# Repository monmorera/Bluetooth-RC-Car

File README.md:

# Bluetooth-RC-Car
### Bluetooth RC Car project for ECE 196 course

#### About:
This project is to create a bluetooth radio-controlled car. The PCB for the vehicle and remote was created and designed with EAGLE. It was then programmed using Arduino. The remote casing and vehicle parts were created and assembled in SolidWorks. Some parts were 3D printed and others laser cut.

##### Vehicle:

##### Remote:

##### Final:

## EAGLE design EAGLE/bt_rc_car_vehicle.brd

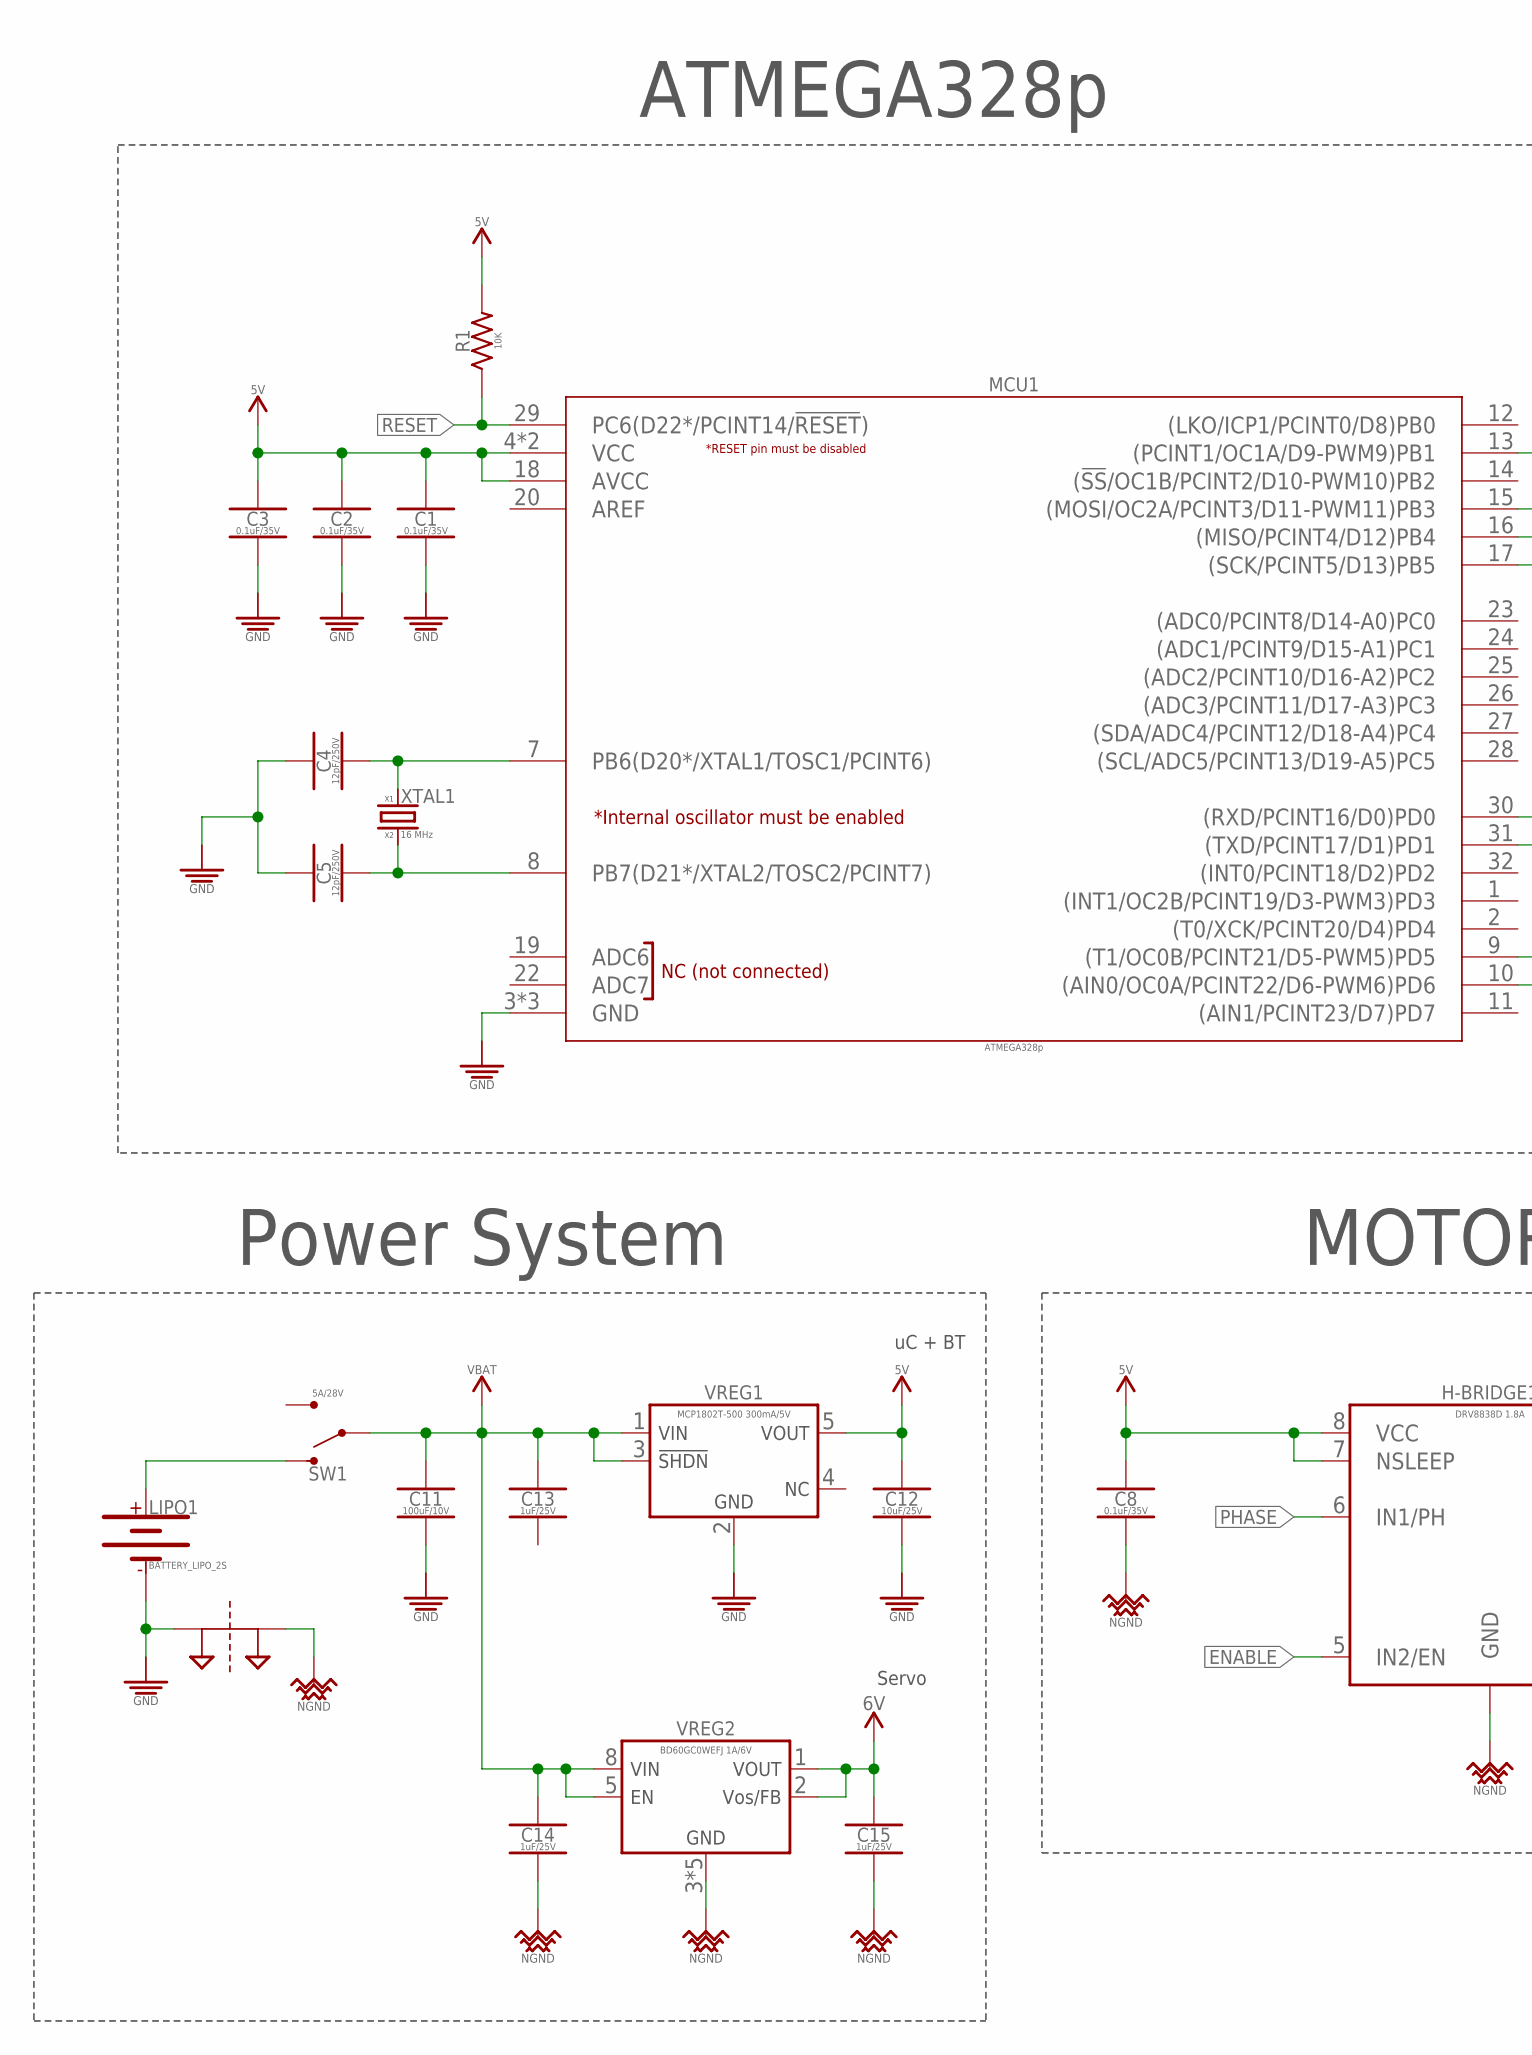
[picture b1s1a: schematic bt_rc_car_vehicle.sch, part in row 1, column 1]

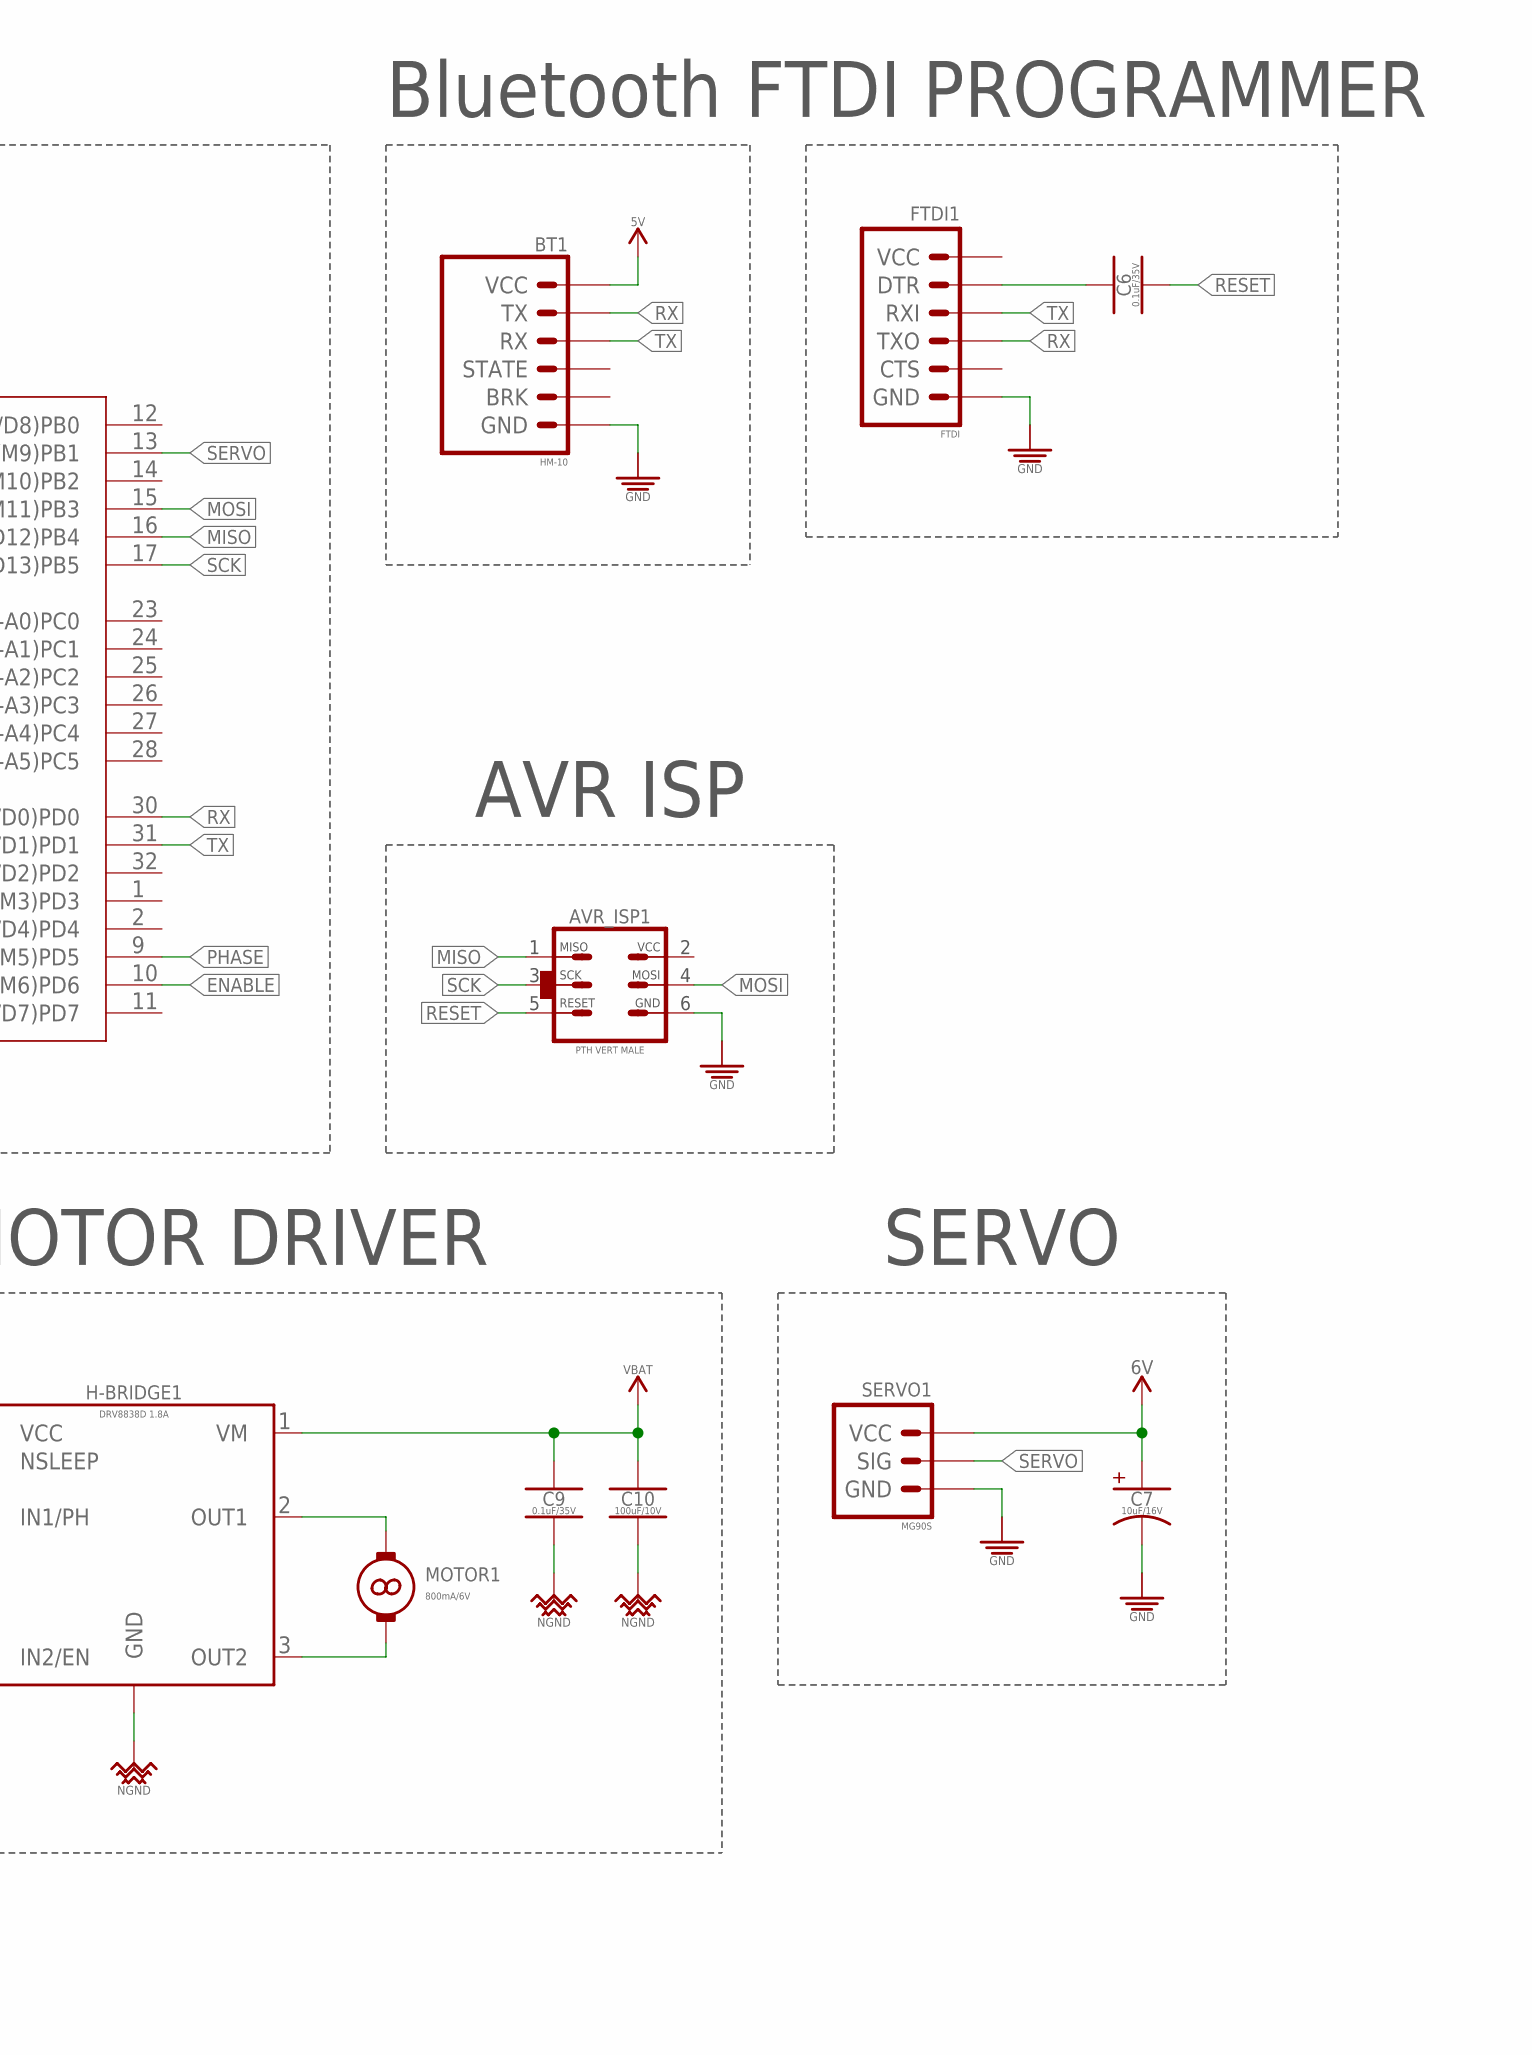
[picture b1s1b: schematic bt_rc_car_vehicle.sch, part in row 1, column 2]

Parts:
AVR_ISP1: PTH VERT MALE; HDRV6W64P254_2X3_762X483X838B_AVR-ISP
BT1: HM-10; HDRVR6W64P254_1X6_1574X254X850B
C1, C2, C3, C6, C8, C9: 0.1uF/35V; CAPC2012X95_SMD-0805
C4, C5: 12pF/250V; CAPC2012X95_SMD-0805
C7: 10uF/16V; CAPMP3216X180_SMD_CAP-TANT-1206
C10, C11: 100uF/10V; CAPC3225X270_SMD-1210
C12: 10uF/25V; CAPC2012X95_SMD-0805
C13, C14, C15: 1uF/25V; CAPC2012X95_SMD-0805
FTDI1: FTDI; HDRV6W64P254_1X6_1524X254X838B_FTDI
H-BRIDGE1: DRV8838D 1.8A; WSON-8-PPAD
LIPO1: BATTERY_LIPO_2S; DUAL_PTH_PADS
MCU1: ATMEGA328p; QFP80P900X900X120-32
MOTOR1: 800mA/6V; CONNECTOR_MOTOR
NET_BRIDGE1: NET_BRIDGE
R1: 10K; RESC2012X60_SMD-0805
SERVO1: MG90S; HDRV3W64P254_1X3_762X254X838B
SW1: 5A/28V; SW_TOGGLE_SPDT_5A-28V_13L-7W
VREG1: MCP1802T-500 300mA/5V; SOT95P280X145-5
VREG2: BD60GC0WEFJ 1A/6V; SOIC127P600X100-8
XTAL1: 16 MHz; OSCCC500X320X110_CRYSTAL

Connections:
5V: BT1.VCC, C1.1, C2.1, C3.1, C8.1, C12.1, H-BRIDGE1.7 (NSLEEP), H-BRIDGE1.8 (VCC), MCU1.4 (VCC), MCU1.6 (VCC), MCU1.18 (AVCC), R1.2, VREG1.5 (VOUT)
6V: C7.A, C15.1, SERVO1.VCC, VREG2.1 (VOUT), VREG2.2 (VOS/FB)
ENABLE: H-BRIDGE1.5 (IN2/EN), MCU1.10 ((AIN0/OC0A/PCINT22/D6-PWM6)PD6)
GND: AVR_ISP1.GND, BT1.GND, C1.2, C2.2, C3.2, C4.1, C5.1, C7.K, C11.2, C12.2, FTDI1.GND, LIPO1.-, MCU1.3 (GND), MCU1.5 (GND), MCU1.21 (GND), NET_BRIDGE1.P$1, SERVO1.GND, VREG1.2 (GND)
MISO: AVR_ISP1.MISO, MCU1.16 ((MISO/PCINT4/D12)PB4)
MOSI: AVR_ISP1.MOSI, MCU1.15 ((MOSI/OC2A/PCINT3/D11-PWM11)PB3)
unnamed: C5.2, MCU1.8 (PB7(D21*/XTAL2/TOSC2/PCINT7)), XTAL1.3 (XTAL2)
unnamed: C4.2, MCU1.7 (PB6(D20*/XTAL1/TOSC1/PCINT6)), XTAL1.1 (XTAL1)
unnamed: C6.1, FTDI1.DTR
unnamed: H-BRIDGE1.2 (OUT1), MOTOR1.+
unnamed: H-BRIDGE1.3 (OUT2), MOTOR1.-
unnamed: LIPO1.+, SW1.S1
NGND: C8.2, C9.2, C10.2, C14.2, C15.2, H-BRIDGE1.4 (GND), H-BRIDGE1.GND, H-BRIDGE1.P$1 (GND), H-BRIDGE1.P$2 (GND), NET_BRIDGE1.P$2, VREG2.3 (GND), VREG2.4 (GND), VREG2.6 (GND), VREG2.7 (GND), VREG2.FIN (GND)
PHASE: H-BRIDGE1.6 (IN1/PH), MCU1.9 ((T1/OC0B/PCINT21/D5-PWM5)PD5)
RESET: AVR_ISP1.RESET, C6.2, MCU1.29 (PC6(D22*/PCINT14/!RESET!)), R1.1
RX: BT1.TX, FTDI1.TX (TXO), MCU1.30 ((RXD/PCINT16/D0)PD0)
SCK: AVR_ISP1.SCK, MCU1.17 ((SCK/PCINT5/D13)PB5)
SERVO: MCU1.13 ((PCINT1/OC1A/D9-PWM9)PB1), SERVO1.SIG
TX: BT1.RX, FTDI1.RX (RXI), MCU1.31 ((TXD/PCINT17/D1)PD1)
VBAT: C9.1, C10.1, C11.1, C13.1, C14.1, H-BRIDGE1.1 (VM), SW1.P, VREG1.1 (VIN), VREG1.3 (!SHDN), VREG2.5 (EN), VREG2.8 (VIN)

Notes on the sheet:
ATMEGA328p
Bluetooth
AVR ISP
FTDI PROGRAMMER
SERVO
MOTOR DRIVER
Power System
Servo
uC + BT

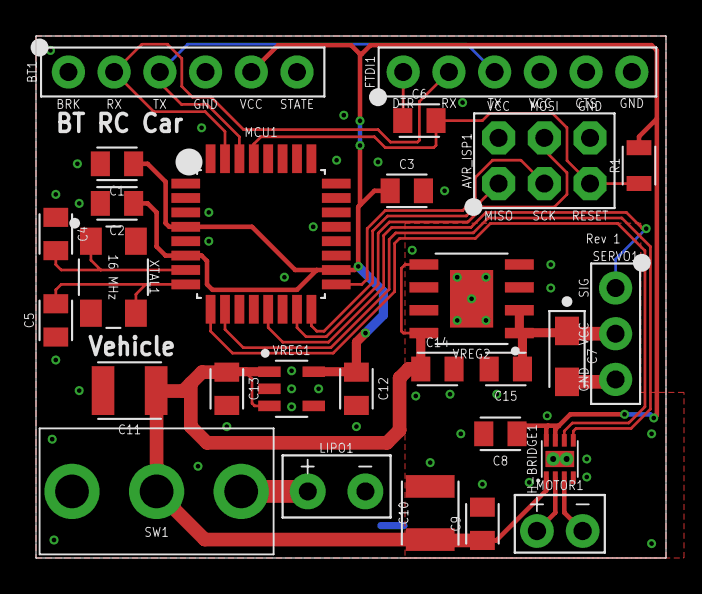
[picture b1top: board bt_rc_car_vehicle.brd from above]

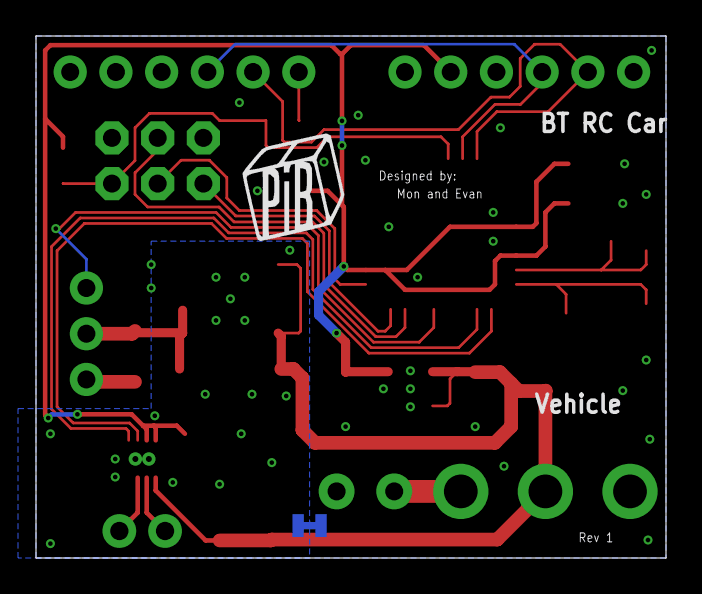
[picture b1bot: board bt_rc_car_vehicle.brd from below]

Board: 2 copper layers, 35.0 x 29.0 mm, 30 parts (2 on the bottom side), 20 nets.

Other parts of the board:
U$1: PIB_LOGO_10MM

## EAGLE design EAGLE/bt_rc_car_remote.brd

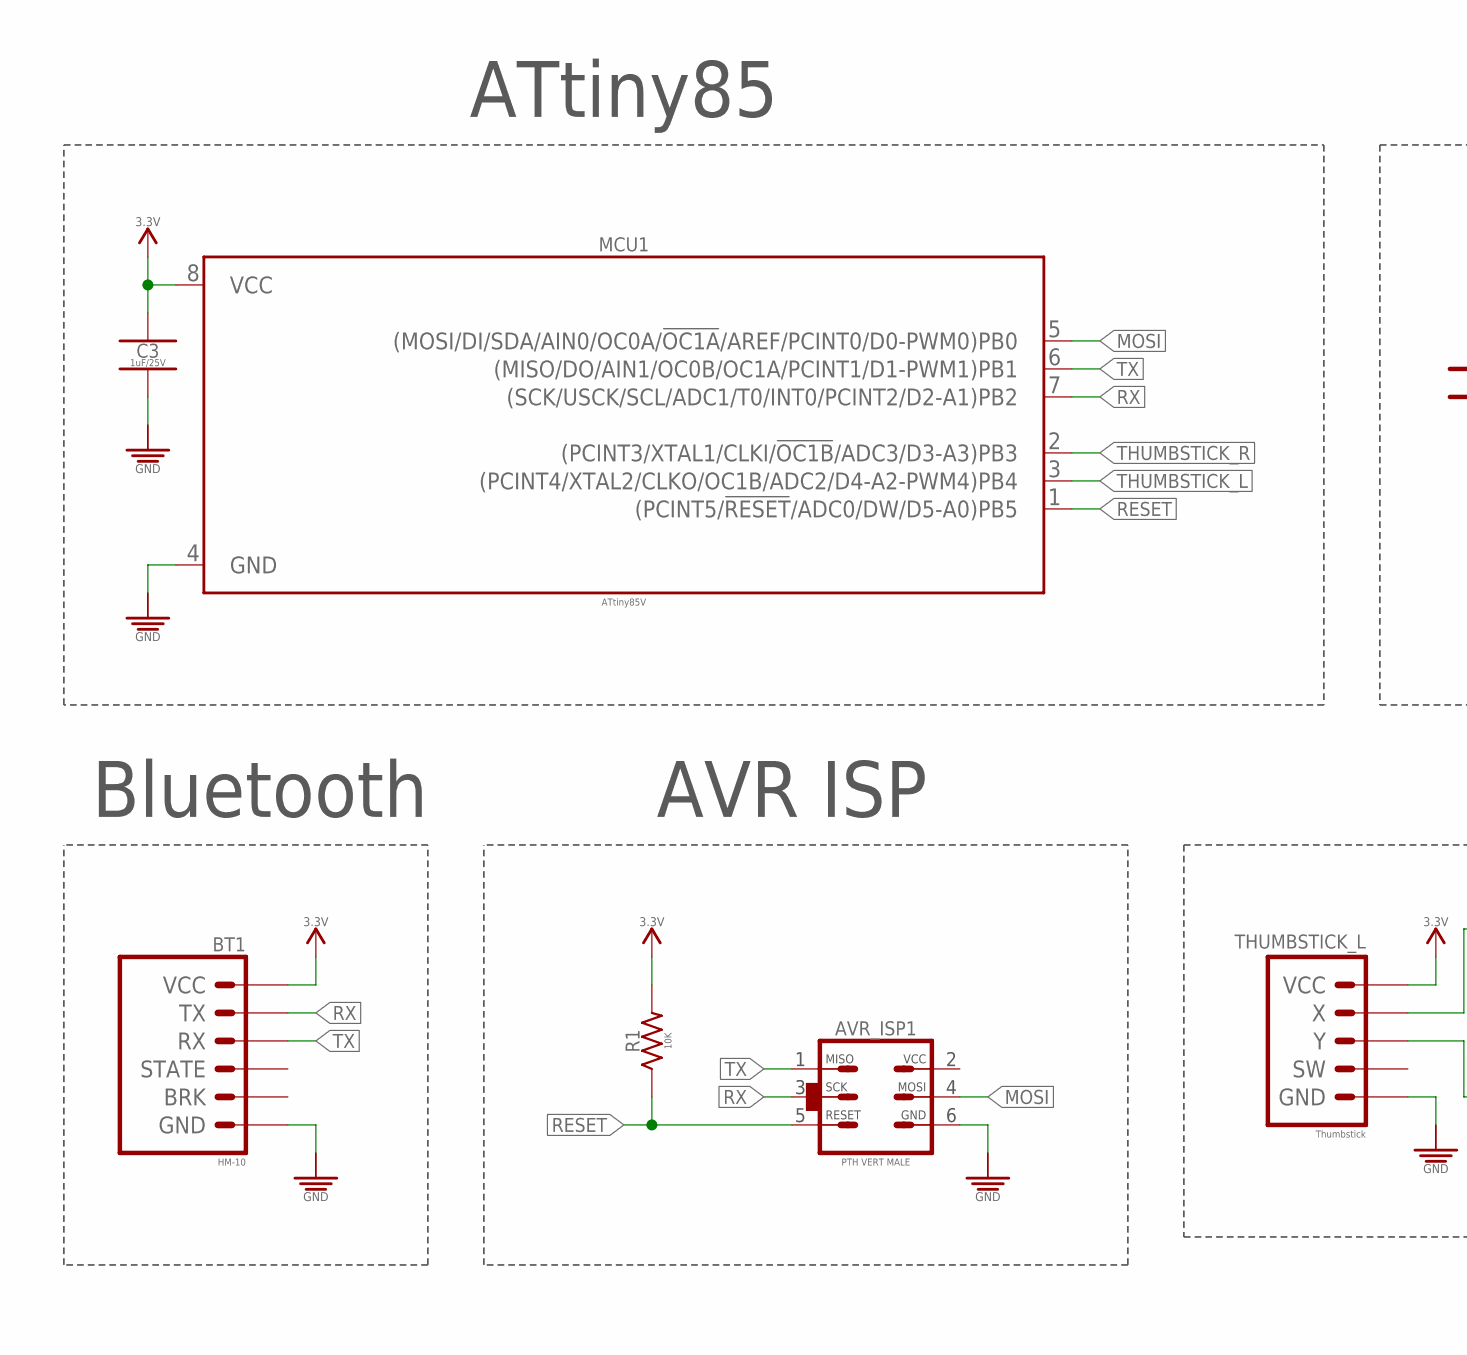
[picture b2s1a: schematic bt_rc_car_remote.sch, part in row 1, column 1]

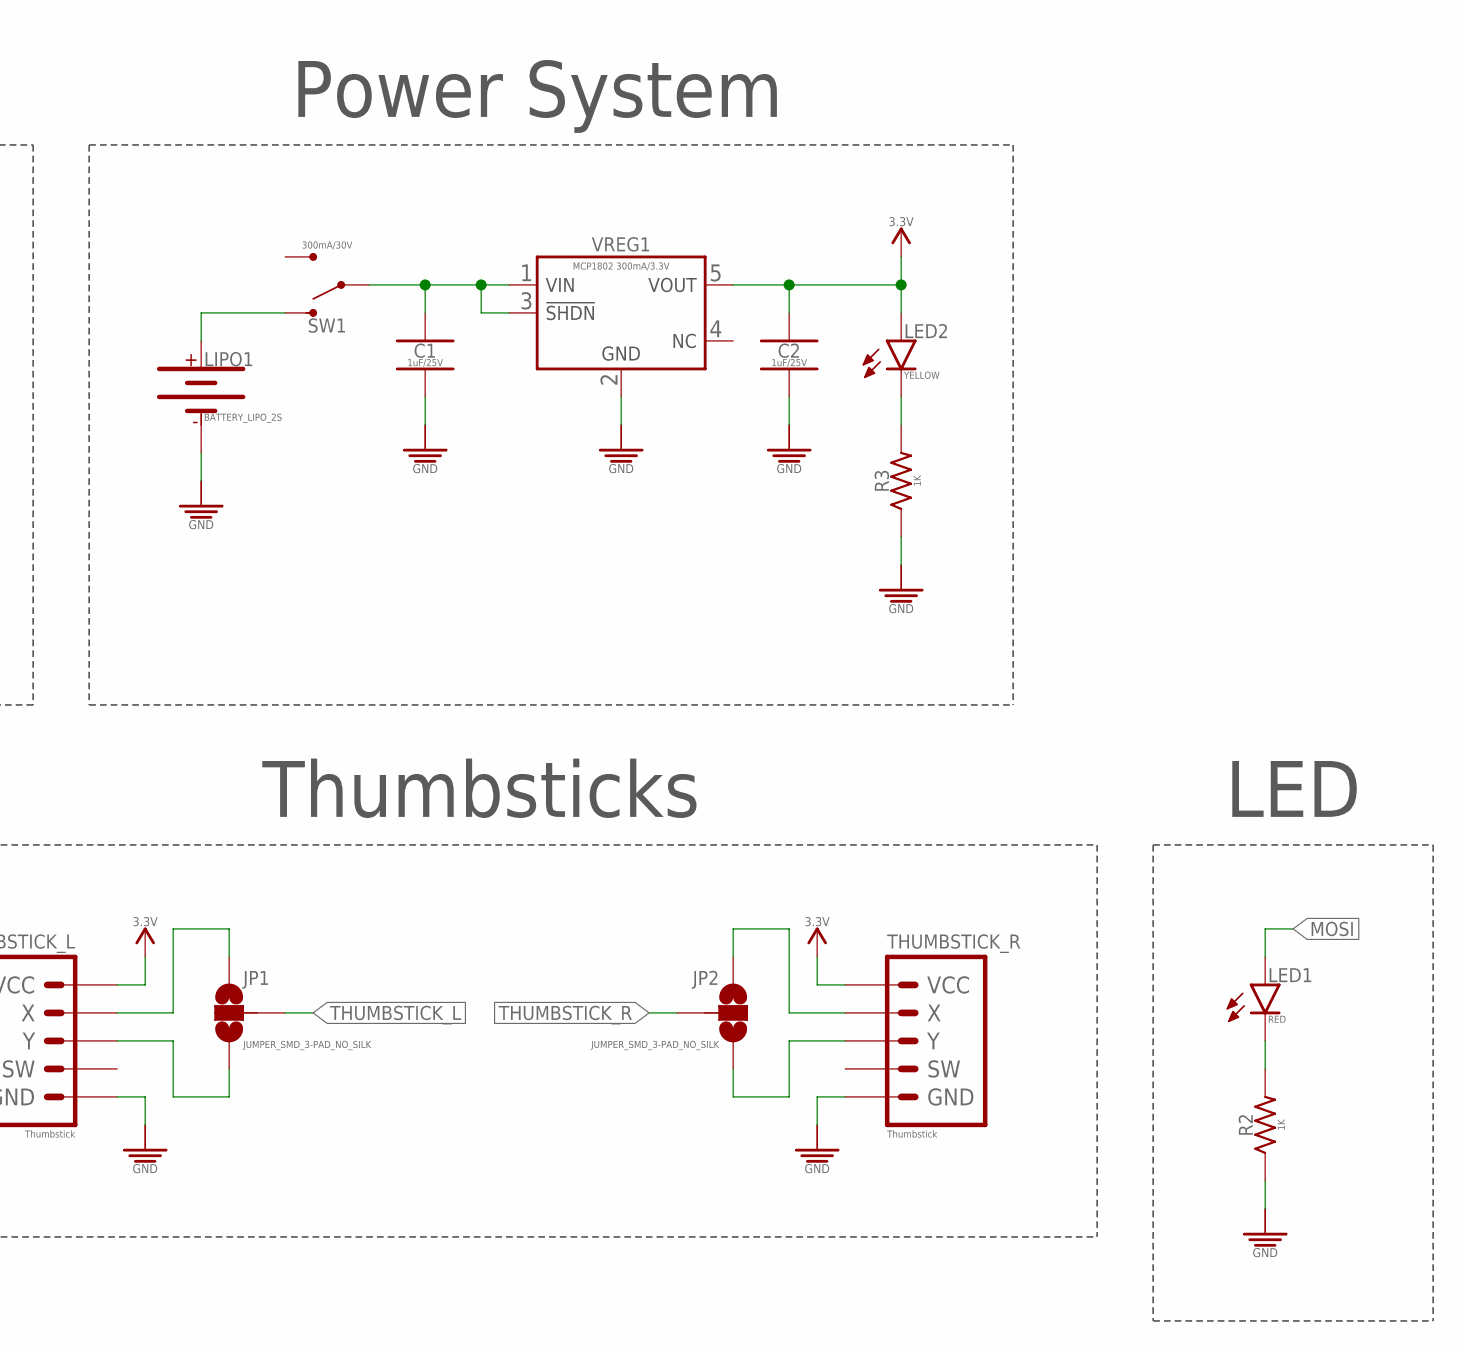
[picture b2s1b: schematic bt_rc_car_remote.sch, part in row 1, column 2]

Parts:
AVR_ISP1: PTH VERT MALE; HDRV6W64P254_2X3_762X483X838B_AVR-ISP
BT1: HM-10; HDRRAR6W60P254_1X6_1574X850X274B
C1, C2, C3: 1uF/25V; CAPC2012X95_SMD-0805
JP1, JP2: JUMPER_SMD_3-PAD_NO_SILK; SMT-JUMPER_3_NO_SILK
LED1: RED; LEDC2012X120_LED-0805
LED2: YELLOW; LEDC2012X120_LED-0805
LIPO1: BATTERY_LIPO_2S; DUAL_PTH_PADS
MCU1: ATtiny85V; SOIC127P798X216-8
R1: 10K; RESC2012X60_SMD-0805
R2, R3: 1K; RESC2012X60_SMD-0805
SW1: 300mA/30V; SW_SLIDE_SPDT_VERT_8.6L-4.3W
THUMBSTICK_L: Thumbstick; HDRRAR5W60P254_1X5_1320X850X274B
THUMBSTICK_R: Thumbstick; HDRRAR5W60P254_1X5_1320X850X274B
VREG1: MCP1802 300mA/3.3V; SOT95P280X145-5

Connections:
3.3V: BT1.VCC, C2.1, C3.1, LED2.A, MCU1.8 (VCC), R1.2, THUMBSTICK_L.VCC, THUMBSTICK_R.VCC, VREG1.5 (VOUT)
GND: AVR_ISP1.GND, BT1.GND, C1.2, C2.2, C3.2, LIPO1.-, MCU1.4 (GND), R2.1, R3.1, THUMBSTICK_L.GND, THUMBSTICK_R.GND, VREG1.2 (GND)
MOSI: AVR_ISP1.MOSI, LED1.A, MCU1.5 ((MOSI/DI/SDA/AIN0/OC0A/!OC1A!/AREF/PCIN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)
unnamed: JP1.1, THUMBSTICK_L.X
unnamed: JP1.3, THUMBSTICK_L.Y
unnamed: JP2.1, THUMBSTICK_R.X
unnamed: JP2.3, THUMBSTICK_R.Y
unnamed: LED1.K, R2.2
unnamed: LIPO1.+, SW1.S1
unnamed: C1.1, SW1.P, VREG1.1 (VIN), VREG1.3 (!SHDN)
unnamed: LED2.K, R3.2
RESET: AVR_ISP1.RESET, MCU1.1 ((PCINT5/!RESET!/ADC0/DW/D5-A0)PB5), R1.1
RX: AVR_ISP1.SCK, BT1.TX, MCU1.7 ((SCK/USCK/SCL/ADC1/T0/INT0/PCINT2/D2-A1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)
THUMBSTICK_L: JP1.2, MCU1.3 ((PCINT4/XTAL2/CLKO/OC1B/ADC2/D4-A2-PWM4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)
THUMBSTICK_R: JP2.2, MCU1.2 ((PCINT3/XTAL1/CLKI/!OC1B!/ADC3/D3-A3)PB3)
TX: AVR_ISP1.MISO, BT1.RX, MCU1.6 ((MISO/DO/AIN1/OC0B/OC1A/PCINT1/D1-PWM1)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)

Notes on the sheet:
ATtiny85
Thumbsticks
Bluetooth
AVR ISP
LED
Power System

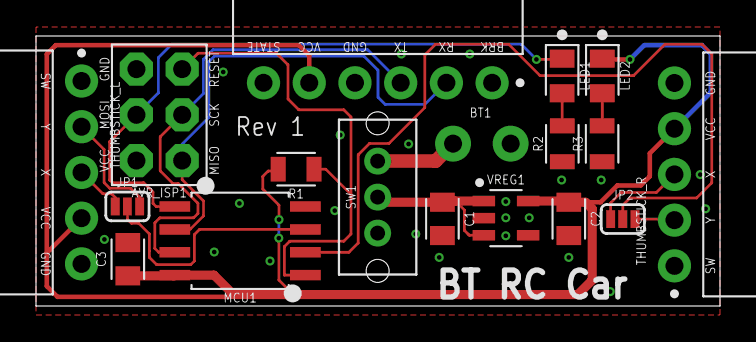
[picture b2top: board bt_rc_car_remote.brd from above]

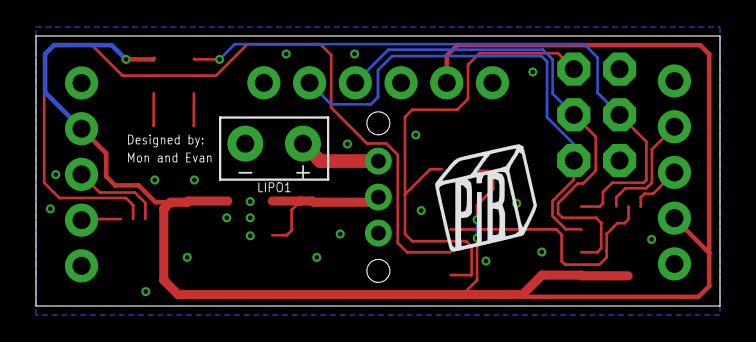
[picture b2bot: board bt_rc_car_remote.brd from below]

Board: 2 copper layers, 38.0 x 15.0 mm, 19 parts (2 on the bottom side), 16 nets.

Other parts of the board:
U$1: PIB_LOGO_10MM

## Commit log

2019-11-09 added hardware files
2019-12-06 Added Arduino Code
